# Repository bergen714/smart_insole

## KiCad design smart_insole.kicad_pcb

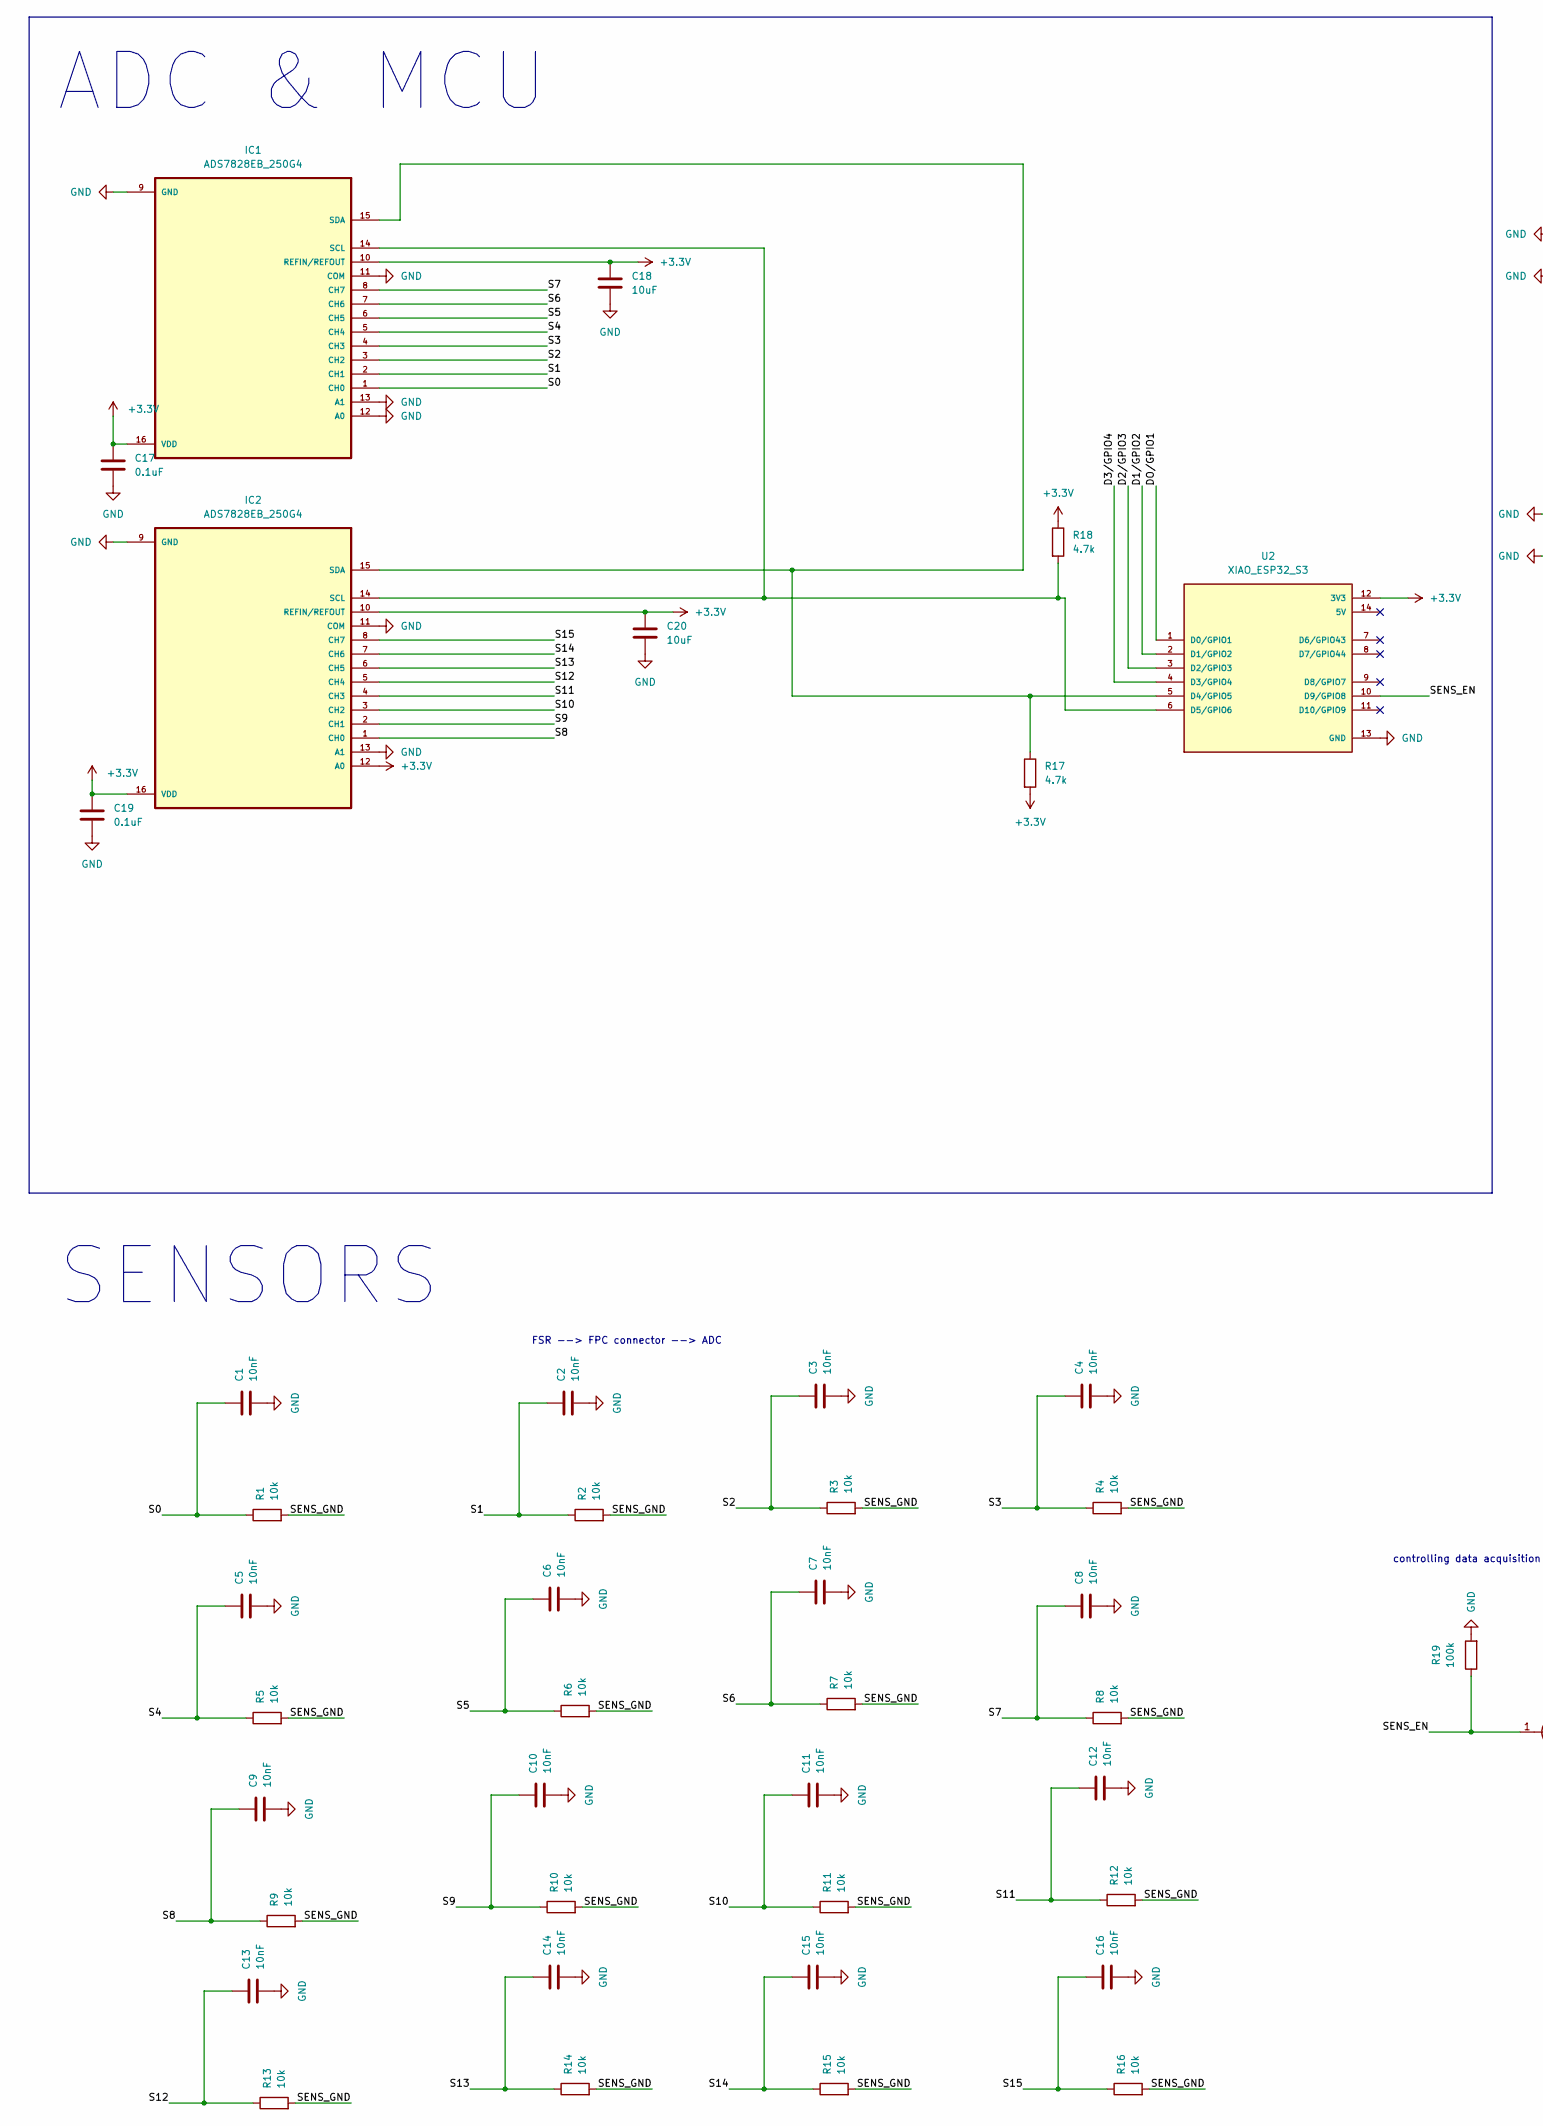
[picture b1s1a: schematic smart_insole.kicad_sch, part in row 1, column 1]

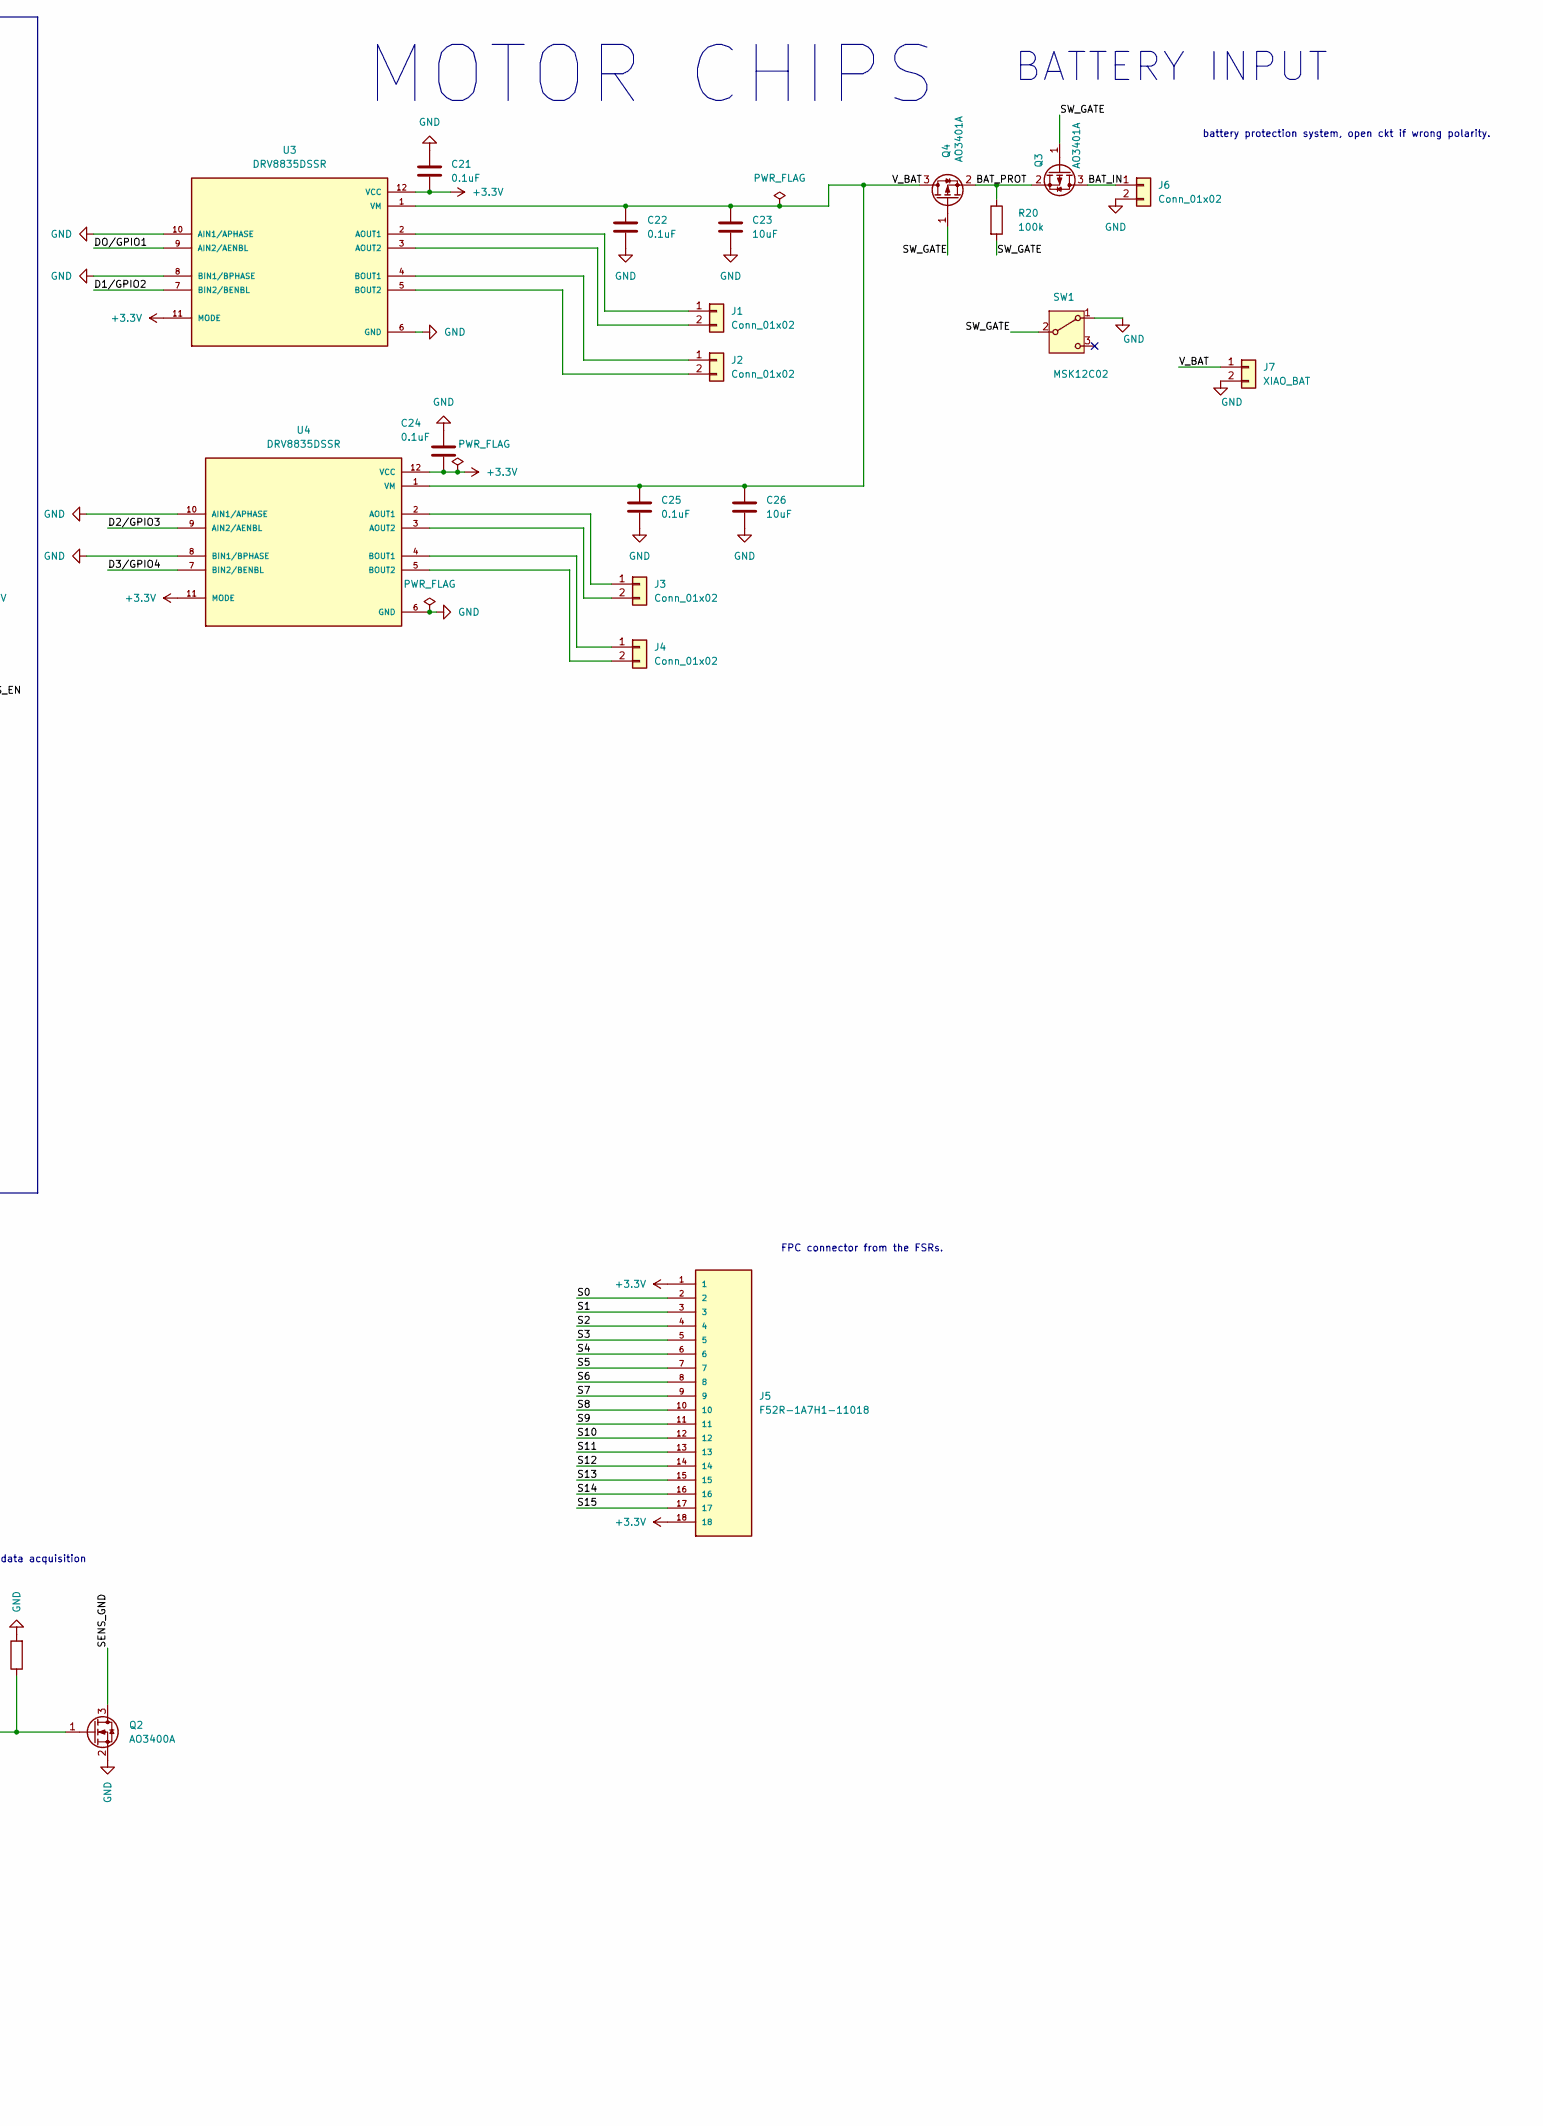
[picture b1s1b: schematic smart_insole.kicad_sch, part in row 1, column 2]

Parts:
C1, C2, C3, C4, C5, C6, C7, C8, C9, C10, C11, C12, C13, C14, C15, C16: 10nF; C0402
C17, C19, C21, C22, C24, C25: 0.1uF; C0402
C18, C20, C23, C26: 10uF; C0603
IC1, IC2: ADS7828EB_250G4; SOP65P640X120-16N
J1, J2, J3, J4, J6: Conn_01x02; CONN-SMD_P2.00_S2B-PH-SM4-TB-LF-SN
J5: F52R-1A7H1-11018; FPC-SMD_18P-P1.00_THD1015-18CL-SN; MPN F52R-1A7H1-11018
J7: XIAO_BAT; PinHeader_1x02_P2.54mm_Vertical
Q2: AO3400A; SOT-23
Q3, Q4: AO3401A; SOT-23; LCSC C15127
R1, R2, R3, R4, R5, R6, R7, R8, R9, R10, R11, R12, R13, R14, R15, R16: 10k; R0402
R17, R18: 4.7k; R0402
R19: 100k; R0402
R20: 100k; R0402; LCSC C25741
SW1: MSK12C02; SW-TH_MSK12C02; LCSC C431540
U2: XIAO_ESP32_S3; MODULE_XIAO_ESP32_S3; PARTREV April 22nd, 2026
U3, U4: DRV8835DSSR; SON50P300X200X80-13N; PARTREV H

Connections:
+3.3V: C17.1, C18.1, C19.1, C20.1, C21.2, C24.2, IC1.10 (REFIN/REFOUT), IC1.16 (VDD), IC2.10 (REFIN/REFOUT), IC2.12 (A0), IC2.16 (VDD), J5.1, J5.18, R17.2, R18.1, U2.12 (3V3), U3.11 (MODE), U3.12 (VCC), U4.11 (MODE), U4.12 (VCC)
/BAT_IN: J6.1, Q3.3 (D)
/BAT_PROT: Q3.2 (S), Q4.2 (S), R20.1
/D1/GPIO2: U2.2 (D1/GPIO2), U3.7 (BIN2/BENBL)
/D2/GPIO3: U2.3 (D2/GPIO3), U4.9 (AIN2/AENBL)
/D3/GPIO4: U2.4 (D3/GPIO4), U4.7 (BIN2/BENBL)
/DO/GPIO1: U2.1 (D0/GPIO1), U3.9 (AIN2/AENBL)
/S0: C1.1, IC1.1 (CH0), J5.2, R1.1
/S1: C2.1, IC1.2 (CH1), J5.3, R2.1
/S2: C3.1, IC1.3 (CH2), J5.4, R3.1
/S3: C4.1, IC1.4 (CH3), J5.5, R4.1
/S4: C5.1, IC1.5 (CH4), J5.6, R5.1
/S5: C6.1, IC1.6 (CH5), J5.7, R6.1
/S6: C7.1, IC1.7 (CH6), J5.8, R7.1
/S7: C8.1, IC1.8 (CH7), J5.9, R8.1
/S8: C9.1, IC2.1 (CH0), J5.10, R9.1
/S9: C10.1, IC2.2 (CH1), J5.11, R10.1
/S10: C11.1, IC2.3 (CH2), J5.12, R11.1
/S11: C12.1, IC2.4 (CH3), J5.13, R12.1
/S12: C13.1, IC2.5 (CH4), J5.14, R13.1
/S13: C14.1, IC2.6 (CH5), J5.15, R14.1
/S14: C15.1, IC2.7 (CH6), J5.16, R15.1
/S15: C16.1, IC2.8 (CH7), J5.17, R16.1
/SENS_EN: Q2.1 (G), R19.1, U2.10 (D9/GPIO8)
/SENS_GND: Q2.3 (D), R1.2, R2.2, R3.2, R4.2, R5.2, R6.2, R7.2, R8.2, R9.2, R10.2, R11.2, R12.2, R13.2, R14.2, R15.2, R16.2
/SW_GATE: Q3.1 (G), Q4.1 (G), R20.2, SW1.2 (B)
/V_BAT: C22.1, C23.1, C25.1, C26.1, J7.1, Q4.3 (D), U3.1 (VM), U4.1 (VM)
GND: C1.2, C2.2, C3.2, C4.2, C5.2, C6.2, C7.2, C8.2, C9.2, C10.2, C11.2, C12.2, C13.2, C14.2, C15.2, C16.2, C17.2, C18.2, C19.2, C20.2, C21.1, C22.2, C23.2, C24.1, C25.2, C26.2, IC1.9 (GND), IC1.11 (COM), IC1.12 (A0), IC1.13 (A1), IC2.9 (GND), IC2.11 (COM), IC2.13 (A1), J6.2, J7.2, Q2.2 (S), R19.2, SW1.1 (A), U2.13 (GND), U3.6 (GND), U3.8 (BIN1/BPHASE), U3.10 (AIN1/APHASE), U3.13 (GND), U4.6 (GND), U4.8 (BIN1/BPHASE), U4.10 (AIN1/APHASE), U4.13 (GND)
unnamed: IC1.14 (SCL), IC2.14 (SCL), R18.2, U2.6 (D5/GPIO6)
unnamed: IC1.15 (SDA), IC2.15 (SDA), R17.1, U2.5 (D4/GPIO5)
unnamed: J1.1, U3.2 (AOUT1)
unnamed: J1.2, U3.3 (AOUT2)
unnamed: J2.1, U3.4 (BOUT1)
unnamed: J2.2, U3.5 (BOUT2)
unnamed: J3.1, U4.2 (AOUT1)
unnamed: J3.2, U4.3 (AOUT2)
unnamed: J4.1, U4.4 (BOUT1)
unnamed: J4.2, U4.5 (BOUT2)

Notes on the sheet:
controlling data acquisition
MOTOR CHIPS
BATTERY INPUT
FPC connector from the FSRs.
ADC & MCU
FSR --> FPC connector --> ADC
SENSORS
battery protection system, open ckt if wrong polarity.

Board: 2 copper layers, 62 parts (0 on the bottom side), 38 nets, no tracks yet.
